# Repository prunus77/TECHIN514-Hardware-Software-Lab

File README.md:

# Hardware and Software Lab - System Design Class

This repository contains code and resources for the Hardware and Software Lab, a hands-on System Design course. The aim of this class is to explore the integration of hardware and software systems, focusing on practical applications, prototyping, and design principles.

Contents

## The repository is organized as follows:

- ├── hardware/              # Hardware design files (e.g., PCB layouts, circuit diagrams, BOMs)
- ├── software/              # Codebase for software modules and system integration
- │   ├── microcontroller/   # Code for microcontroller programming (e.g., Arduino, Raspberry Pi)
- │   ├── app/               # Software for desktop or mobile applications interacting with the hardware
- │   └── api/               # API or middleware for hardware-software communication
- ├── docs/                  # Documentation, research papers, and study materials
- ├── experiments/           # Prototyping and lab experiments
- ├── tests/                 # Test scripts and files for validation
- ├── tools/                 # Custom scripts and utilities
- └── README.md              # Repository overview and instructions

## Getting Started

Prerequisites
	•	Hardware: Specify any required hardware components (e.g., microcontrollers, sensors, actuators, development kits).
	•	Software: List the programming languages, IDEs, or tools used (e.g., Python, Arduino IDE, C++, Visual Studio Code).

Installation
	1.	Clone this repository:

git clone https://github.com/your-username/hardware-software-lab.git
cd hardware-software-lab

	2.	Follow setup instructions for specific directories:
	•	For microcontroller code, see hardware/README.md.
	•	For API and middleware, see software/api/README.md.
	3.	Install any necessary dependencies:

pip install -r requirements.txt

or refer to installation instructions in the relevant subdirectory.

Usage
	1.	Compile and upload microcontroller code to the specified device.
	2.	Run the API server or middleware for communication between software and hardware components.
	3.	Interact with the system through the application or test scripts in the tests/ directory.

Contribution Guidelines

We welcome contributions to improve and expand the lab repository. Please adhere to the following:
	1.	Fork the repository and create a new branch for your changes:

git checkout -b feature/your-feature-name

	2.	Test your code thoroughly before submitting a pull request.
	3.	Follow the coding style and conventions used in the project.
	4.	Provide detailed documentation for any new features.

License

This project is licensed under the MIT License. See the LICENSE file for details.

Contact

For queries or suggestions, please contact [Your Name] at [your-email@example.com].

Happy coding and designing! 🚀

# This text and structure has been generated by ChatGPT
## Cintent generated to populate the README file

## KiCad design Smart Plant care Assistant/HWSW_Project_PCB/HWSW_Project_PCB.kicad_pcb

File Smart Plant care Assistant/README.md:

# Smart Plant Care Assistant
As plant owners we often forget to give good care to the plants. This project monitors soil moisture, temperature, and ambient light to provide actionable insights for optimal plant care. 

The system uses sensors to collect data and a display device for real-time feedback.
Below is the sketch to the conceotual sketch of the device system:

## Sensor Device
The sensor device collects environmental data using soil moisture, temperature, and ambient light sensors. It sends this data via BLE to the display device. The sensors are powered by a rechargeable battery with USB charging capabilities.

Below are the features of the Sensor Device:

- Sensors: Soil moisture, temperature, ambient light.
- Wireless module: Bluetooth Low Energy (BLE).
- Power source: Rechargeable battery.
- Enclosure: Portable and weather-resistant.
 
Below is the Picture:

## Display Device
The display device receives data from the sensor device via BLE and visualizes it. A gauge needle shows soil moisture levels, LEDs indicate environmental conditions (e.g., too hot, too dry), and a button allows users to interact with the system. The device is powered by a thoughtfully sized battery with USB charging.

Below are the features of the Sensor Device:

- Stepper motor-driven needle gauge: Indicates the level of care needed
- LED indicators: Indicates the if plant needs watering
- Button for user interactions: Users can reset the specific plants reminder on the disply when care has been given to the plant
- Enclosure design: Will Probably be made out of wood. And will have magnets to stick on metalic surfaces of daily use such as refrigerator door.

## Communication and System Diagram
- Figure 1: Communication diagram showing how the sensor and display devices interact via BLE.

- Figure 2: Detailed system architecture showing sensors, microcontroller, wireless communication, and power flow.

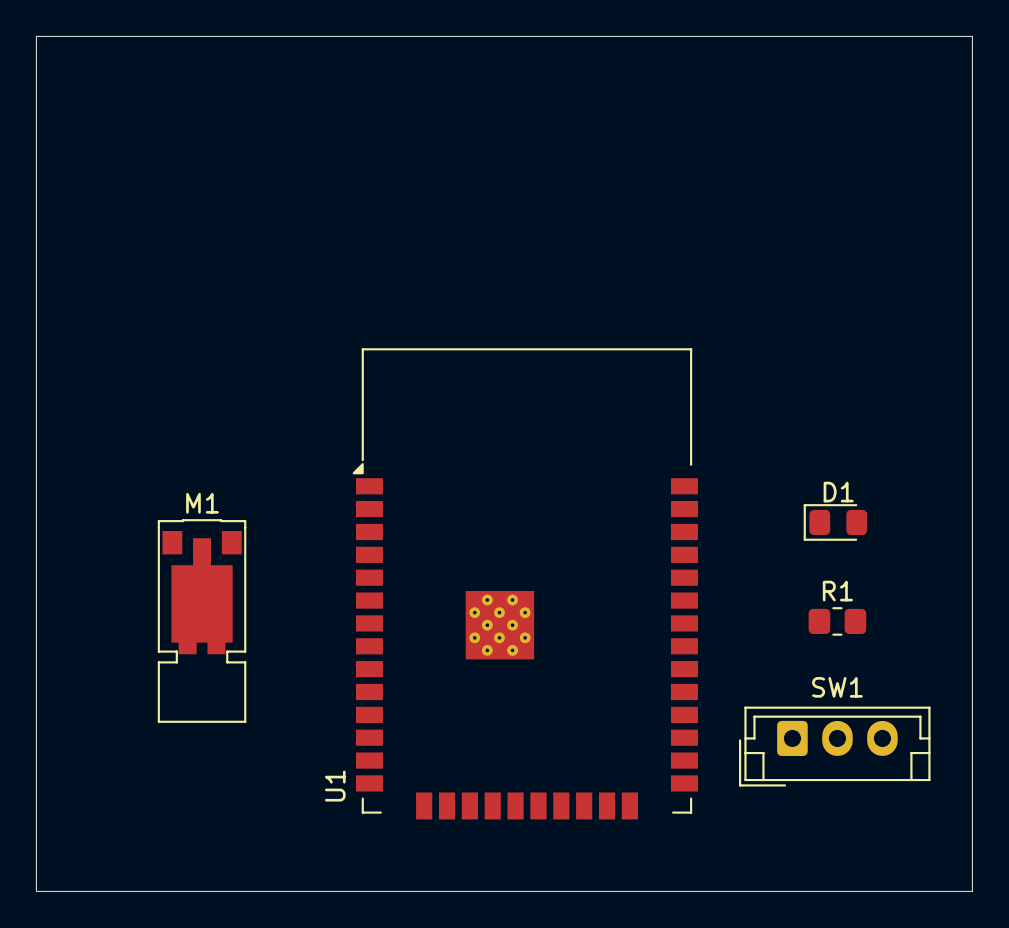
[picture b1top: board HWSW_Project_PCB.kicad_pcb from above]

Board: 2 copper layers, 52.0 x 47.5 mm, 5 parts (0 on the bottom side), 6 nets, no tracks yet.

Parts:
D1: LED; LED_0805_2012Metric_Pad1.15x1.40mm_HandSolder
M1: Stepper_Motor_bipolar; Vybronics_VZ30C1T8219732L
R1: R; R_0805_2012Metric_Pad1.20x1.40mm_HandSolder
SW1: SW_SPDT; JST_EH_B3B-EH-A_1x03_P2.50mm_Vertical
U1: ESP32-WROOM-32E; ESP32-WROOM-32D

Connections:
GND: D1.1 (K), U1.1 (GND), U1.15 (GND), U1.38 (GND), U1.39 (GND)
unnamed: D1.2 (A), R1.2
unnamed: M1.2 (-), U1.8 (IO32)
unnamed: R1.1, SW1.1 (A)
unnamed: SW1.3 (C), U1.2 (VDD)
unnamed: M1.1, U1.9 (IO33)

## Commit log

2025-01-09 Readme Update
2025-01-09 PlatformIO files
2025-01-09 Creating separate folder for labwork
2025-01-21 Committing README file
2025-01-21 Committing changes to README
2025-01-22 Lab2 code folder commit
2025-01-22 Commiting Changes
2025-01-22 Add image to repository
2025-01-24 Adding the pictures file
2025-01-24 Uploading data sheet folder
2025-01-24 Committing changes
2025-01-24 Remove folder System Architecture Diagram from repository
2025-01-24 Changes to Readme
2025-01-29 Adding KiCAD files
2025-01-29 Changes to Folder data
2025-03-11 Adding Sensor Code
